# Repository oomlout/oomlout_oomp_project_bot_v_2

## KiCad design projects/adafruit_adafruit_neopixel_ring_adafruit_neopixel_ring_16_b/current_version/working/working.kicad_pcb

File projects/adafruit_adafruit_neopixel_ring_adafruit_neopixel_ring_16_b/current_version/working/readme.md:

# adafruit_neopixel_ring
 
## summary 
* id: adafruit_adafruit_neopixel_ring_adafruit_neopixel_ring_16_b
* user: adafruit
* name: adafruit_neopixel_ring
* board: adafruit_neopixel_ring_16_b
* repo: https://github.com/adafruit/Adafruit-NeoPixel-Ring

* src_file_repo_sch: 
* src_file_repo_sch_link: https://github.com/adafruit/Adafruit-NeoPixel-Ring/tree/master/
* full details link: https://github.com/oomlout/oomlout_oomp_project_bot_v_2/tree/main/projects/adafruit_adafruit_neopixel_ring_adafruit_neopixel_ring_16_b/current_version/working  

## schematic  
  
[schematic (pdf)](working_schematic.pdf) 

## pcb  

[board (pdf)](working.pdf)  

## working_bom
| Id | Designator | Footprint | Quantity | Designation | Supplier and ref |  | None | 
| --- | --- | --- | --- | --- | --- | --- | --- | 
| 1 | C6,C10,C12,C8,C9,C2,C3,C4 | C0603 | 8 |  |  |  | [''] | 
| 2 | LED11,LED2,LED9,LED4,LED6,LED1,LED10,LED12,LED7,LED3,LED5,LED8 | WS28115050 | 12 | WS28115050 |  |  | [''] | 
| 3 | JP1,JP2,JP3,JP4 | 1X01-CLEANBIG | 4 |  |  |  | [''] | 
| 4 | U$1,U$2 | GUIDE-STAR-12 | 2 |  |  |  | [''] | 
| 5 | U$3 | ADAFRUIT_5MM | 1 |  |  |  | [''] | 

## bom_schematic
| Ref | Qnty | Value | Cmp name | Footprint | Description | Vendor | DNP | 
| --- | --- | --- | --- | --- | --- | --- | --- | 
| C2, C3, C4, C6, C8, C9, C10, C12 | 8 | C-EUC0603 | C-EUC0603 | working:C0603 |  |  |  | 
| JP1, JP2, JP3, JP4 | 4 | PINHD-1X1CB | PINHD-1X1CB | working:1X01-CLEANBIG |  |  |  | 
| LED1, LED2, LED3, LED4, LED5, LED6, LED7, LED8, LED9, LED10, LED11, LED12 | 12 | WS28115050 | WS28115050 | working:WS28115050 |  |  |  |

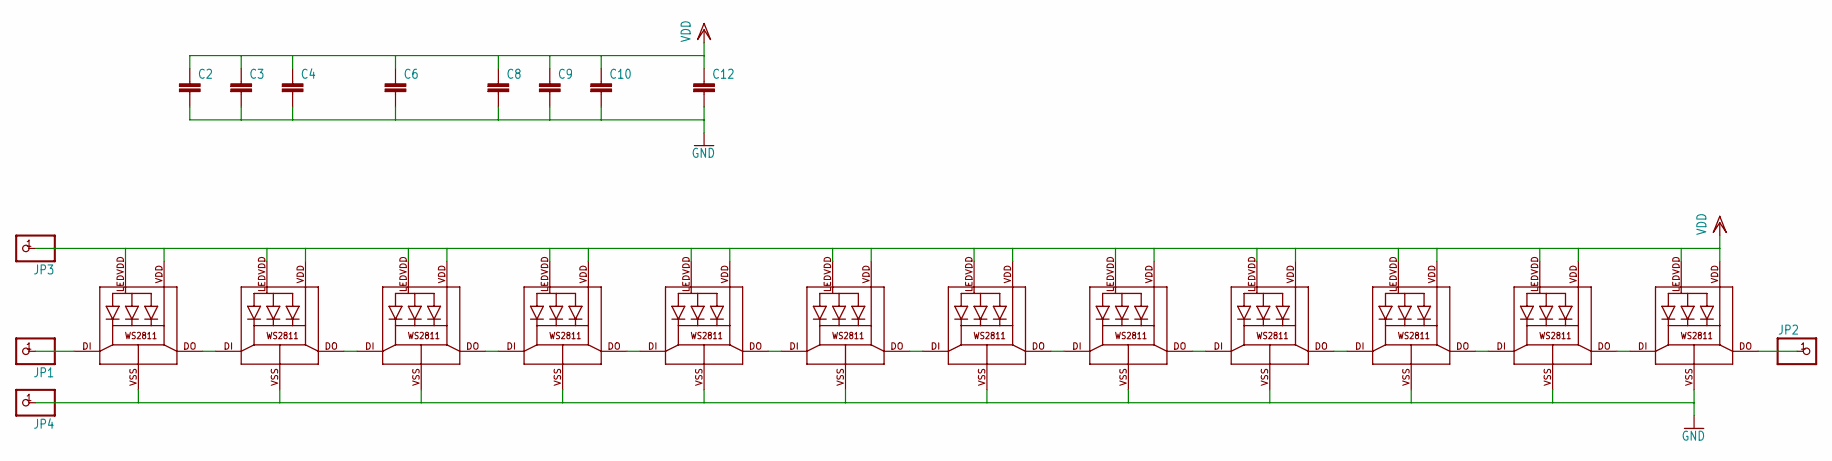
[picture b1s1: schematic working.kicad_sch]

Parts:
C2, C3, C4, C6, C8, C9, C10, C12: C-EUC0603; C0603
JP1, JP2, JP3, JP4: PINHD-1X1CB; 1X01-CLEANBIG
LED1, LED2, LED3, LED4, LED5, LED6, LED7, LED8, LED9, LED10, LED11, LED12: WS28115050

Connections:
GND: C2.2, C3.2, C4.2, C6.2, C8.2, C9.2, C10.2, C12.2, JP4.1, LED1.VSS (GND), LED2.VSS (GND), LED3.VSS (GND), LED4.VSS (GND), LED5.VSS (GND), LED6.VSS (GND), LED7.VSS (GND), LED8.VSS (GND), LED9.VSS (GND), LED10.VSS (GND), LED11.VSS (GND), LED12.VSS (GND)
unnamed: LED1.DO, LED2.DI
unnamed: LED2.DO, LED3.DI
unnamed: LED3.DO, LED4.DI
unnamed: LED4.DO, LED5.DI
unnamed: LED5.DO, LED6.DI
unnamed: LED6.DO, LED7.DI
unnamed: LED7.DO, LED8.DI
unnamed: LED8.DO, LED9.DI
unnamed: LED9.DO, LED10.DI
unnamed: LED10.DO, LED11.DI
unnamed: LED11.DO, LED12.DI
unnamed: JP1.1, LED1.DI
unnamed: JP2.1, LED12.DO
VDD: C2.1, C3.1, C4.1, C6.1, C8.1, C9.1, C10.1, C12.1, JP3.1, LED1.LEDVDD, LED1.VDD, LED2.LEDVDD, LED2.VDD, LED3.LEDVDD, LED3.VDD, LED4.LEDVDD, LED4.VDD, LED5.LEDVDD, LED5.VDD, LED6.LEDVDD, LED6.VDD, LED7.LEDVDD, LED7.VDD, LED8.LEDVDD, LED8.VDD, LED9.LEDVDD, LED9.VDD, LED10.LEDVDD, LED10.VDD, LED11.LEDVDD, LED11.VDD, LED12.LEDVDD, LED12.VDD

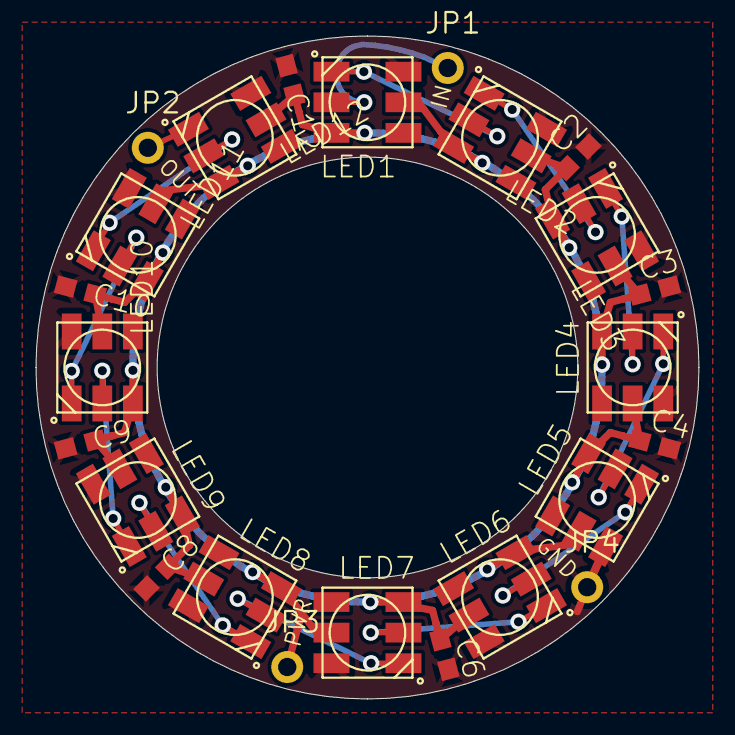
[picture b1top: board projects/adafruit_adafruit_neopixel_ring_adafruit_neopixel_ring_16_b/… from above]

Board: 2 copper layers, 36.8 x 36.8 mm, 27 parts (1 on the bottom side), 15 nets.

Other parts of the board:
U$1, U$2: GUIDE-STAR-12
U$3: ADAFRUIT_5MM

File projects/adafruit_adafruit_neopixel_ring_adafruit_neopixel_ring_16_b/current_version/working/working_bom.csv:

"Id";"Designator";"Footprint";"Quantity";"Designation";"Supplier and ref";
1;"C6,C10,C12,C8,C9,C2,C3,C4";"C0603";8;"";;;
2;"LED11,LED2,LED9,LED4,LED6,LED1,LED10,LED12,LED7,LED3,LED5,LED8";"WS28115050";12;"WS28115050";;;
3;"JP1,JP2,JP3,JP4";"1X01-CLEANBIG";4;"";;;
4;"U$1,U$2";"GUIDE-STAR-12";2;"";;;
5;"U$3";"ADAFRUIT_5MM";1;"";;;

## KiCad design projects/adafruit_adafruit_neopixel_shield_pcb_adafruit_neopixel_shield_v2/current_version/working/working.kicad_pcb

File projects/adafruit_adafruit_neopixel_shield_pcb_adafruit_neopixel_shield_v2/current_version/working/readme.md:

# adafruit_neopixel_shield_pcb
 
## summary 
* id: adafruit_adafruit_neopixel_shield_pcb_adafruit_neopixel_shield_v2
* user: adafruit
* name: adafruit_neopixel_shield_pcb
* board: adafruit_neopixel_shield_v2
* repo: https://github.com/adafruit/Adafruit-NeoPixel-Shield-PCB

* src_file_repo_sch: 
* src_file_repo_sch_link: https://github.com/adafruit/Adafruit-NeoPixel-Shield-PCB/tree/master/
* full details link: https://github.com/oomlout/oomlout_oomp_project_bot_v_2/tree/main/projects/adafruit_adafruit_neopixel_shield_pcb_adafruit_neopixel_shield_v2/current_version/working  

## schematic  
  
[schematic (pdf)](working_schematic.pdf) 

## pcb  

[board (pdf)](working.pdf)  

## working_bom
| Id | Designator | Footprint | Quantity | Designation | Supplier and ref |  | None | 
| --- | --- | --- | --- | --- | --- | --- | --- | 
| 1 | C28,C15,R1,C12,C11,C33,C17,C3,C27,C14,C20,C32,C6,C7,C26,C23,C8,C5,C24,C30,C29,C35,C18,C13,C1,C25,C2,C21,C34,C4,C22,C9,C16,C10,C19,C31 | _0805NO | 36 |  |  |  | [''] | 
| 2 | @HOLE3,@HOLE2,@HOLE0,@HOLE1 |  | 4 |  |  |  | [''] | 
| 3 | Q1 | SOT23-WIDE | 1 | IRLML6401 |  |  | [''] | 
| 4 | LED36,LED24,LED6,LED22,LED16,LED1,LED40,LED31,LED19,LED38,LED10,LED7,LED15,LED25,LED21,LED17,LED30,LED3,LED39,LED27,LED12,LED4,LED29,LED23,LED5,LED28,LED26,LED18,LED2,LED14,LED34,LED35,LED9,LED8,LED37,LED11,LED13,LED33,LED32,LED20 | WS2812B | 40 | WS2812B5050 |  |  | [''] | 
| 5 | FID2,FID1,FID3 | FIDUCIAL_1MM | 3 | FIDUCIAL" |  |  | [''] | 
| 6 | U$1 | ADAFRUIT_5MM | 1 |  |  |  | [''] | 
| 7 | SW1 | EVQ-Q2 | 1 | SPST_TACT-EVQQ2 |  |  | [''] | 
| 8 | JP1 | 1X02_ROUND | 1 |  |  |  | [''] | 
| 9 | JP2 | 1X01-CLEANBIG | 1 |  |  |  | [''] | 
| 10 | U1 | ARDUINOR3-BPLACE | 1 | ARDUINOR3-BPLACE |  |  | [''] | 
| 11 | J1 | 1X2-3.5MM | 1 | 1X2-3.5MM |  |  | [''] | 
| 12 | SJ1 | SOLDERJUMPER_CLOSEDWIRE | 1 |  |  |  | [''] | 
| 13 | U$2 | ADAFRUIT_TEXT_30MM | 1 |  |  |  | [''] | 

## bom_schematic
| Ref | Qnty | Value | Cmp name | Footprint | Description | Vendor | DNP | 
| --- | --- | --- | --- | --- | --- | --- | --- | 
| C1, C2, C3, C4, C5, C6, C7, C8, C9, C10, C11, C12, C13, C14, C15, C16, C17, C18, C19, C20, C21, C22, C23, C24, C25, C26, C27, C28, C29, C30, C31, C32, C33, C34, C35 | 35 | CAP_CERAMIC_0805NO | CAP_CERAMIC_0805NO | working:_0805NO |  |  |  | 
| FID1, FID2, FID3 | 3 | FIDUCIAL"" | FIDUCIAL{dblquote}{dblquote} | working:FIDUCIAL_1MM |  |  |  | 
| J1 | 1 | 1X2-3.5MM | 1X2-3.5MM | working:1X2-3.5MM |  |  |  | 
| JP1 | 1 | HEADER-1X2ROUND | HEADER-1X2ROUND | working:1X02_ROUND |  |  |  | 
| JP2 | 1 | PINHD-1X1CB | PINHD-1X1CB | working:1X01-CLEANBIG |  |  |  | 
| LED1, LED2, LED3, LED4, LED5, LED6, LED7, LED8, LED9, LED10, LED11, LED12, LED13, LED14, LED15, LED16, LED17, LED18, LED19, LED20, LED21, LED22, LED23, LED24, LED25, LED26, LED27, LED28, LED29, LED30, LED31, LED32, LED33, LED34, LED35, LED36, LED37, LED38, LED39, LED40 | 40 | WS2812B5050 | WS2812B5050 | working:WS2812B |  |  |  | 
| Q1 | 1 | IRLML6401 | MOSFET-PWIDE | working:SOT23-WIDE |  |  |  | 
| R1 | 1 | RESISTOR_0805NO | RESISTOR_0805NO | working:_0805NO |  |  |  | 
| SJ1 | 1 | SOLDERJUMPERCLOSED | SOLDERJUMPERCLOSED | working:SOLDERJUMPER_CLOSEDWIRE |  |  |  | 
| SW1 | 1 | SPST_TACT-EVQQ2 | SPST_TACT-EVQQ2 | working:EVQ-Q2 |  |  |  | 
| U1 | 1 | ARDUINOR3-BPLACE | ARDUINOR3-BPLACE | working:ARDUINOR3-BPLACE |  |  |  |

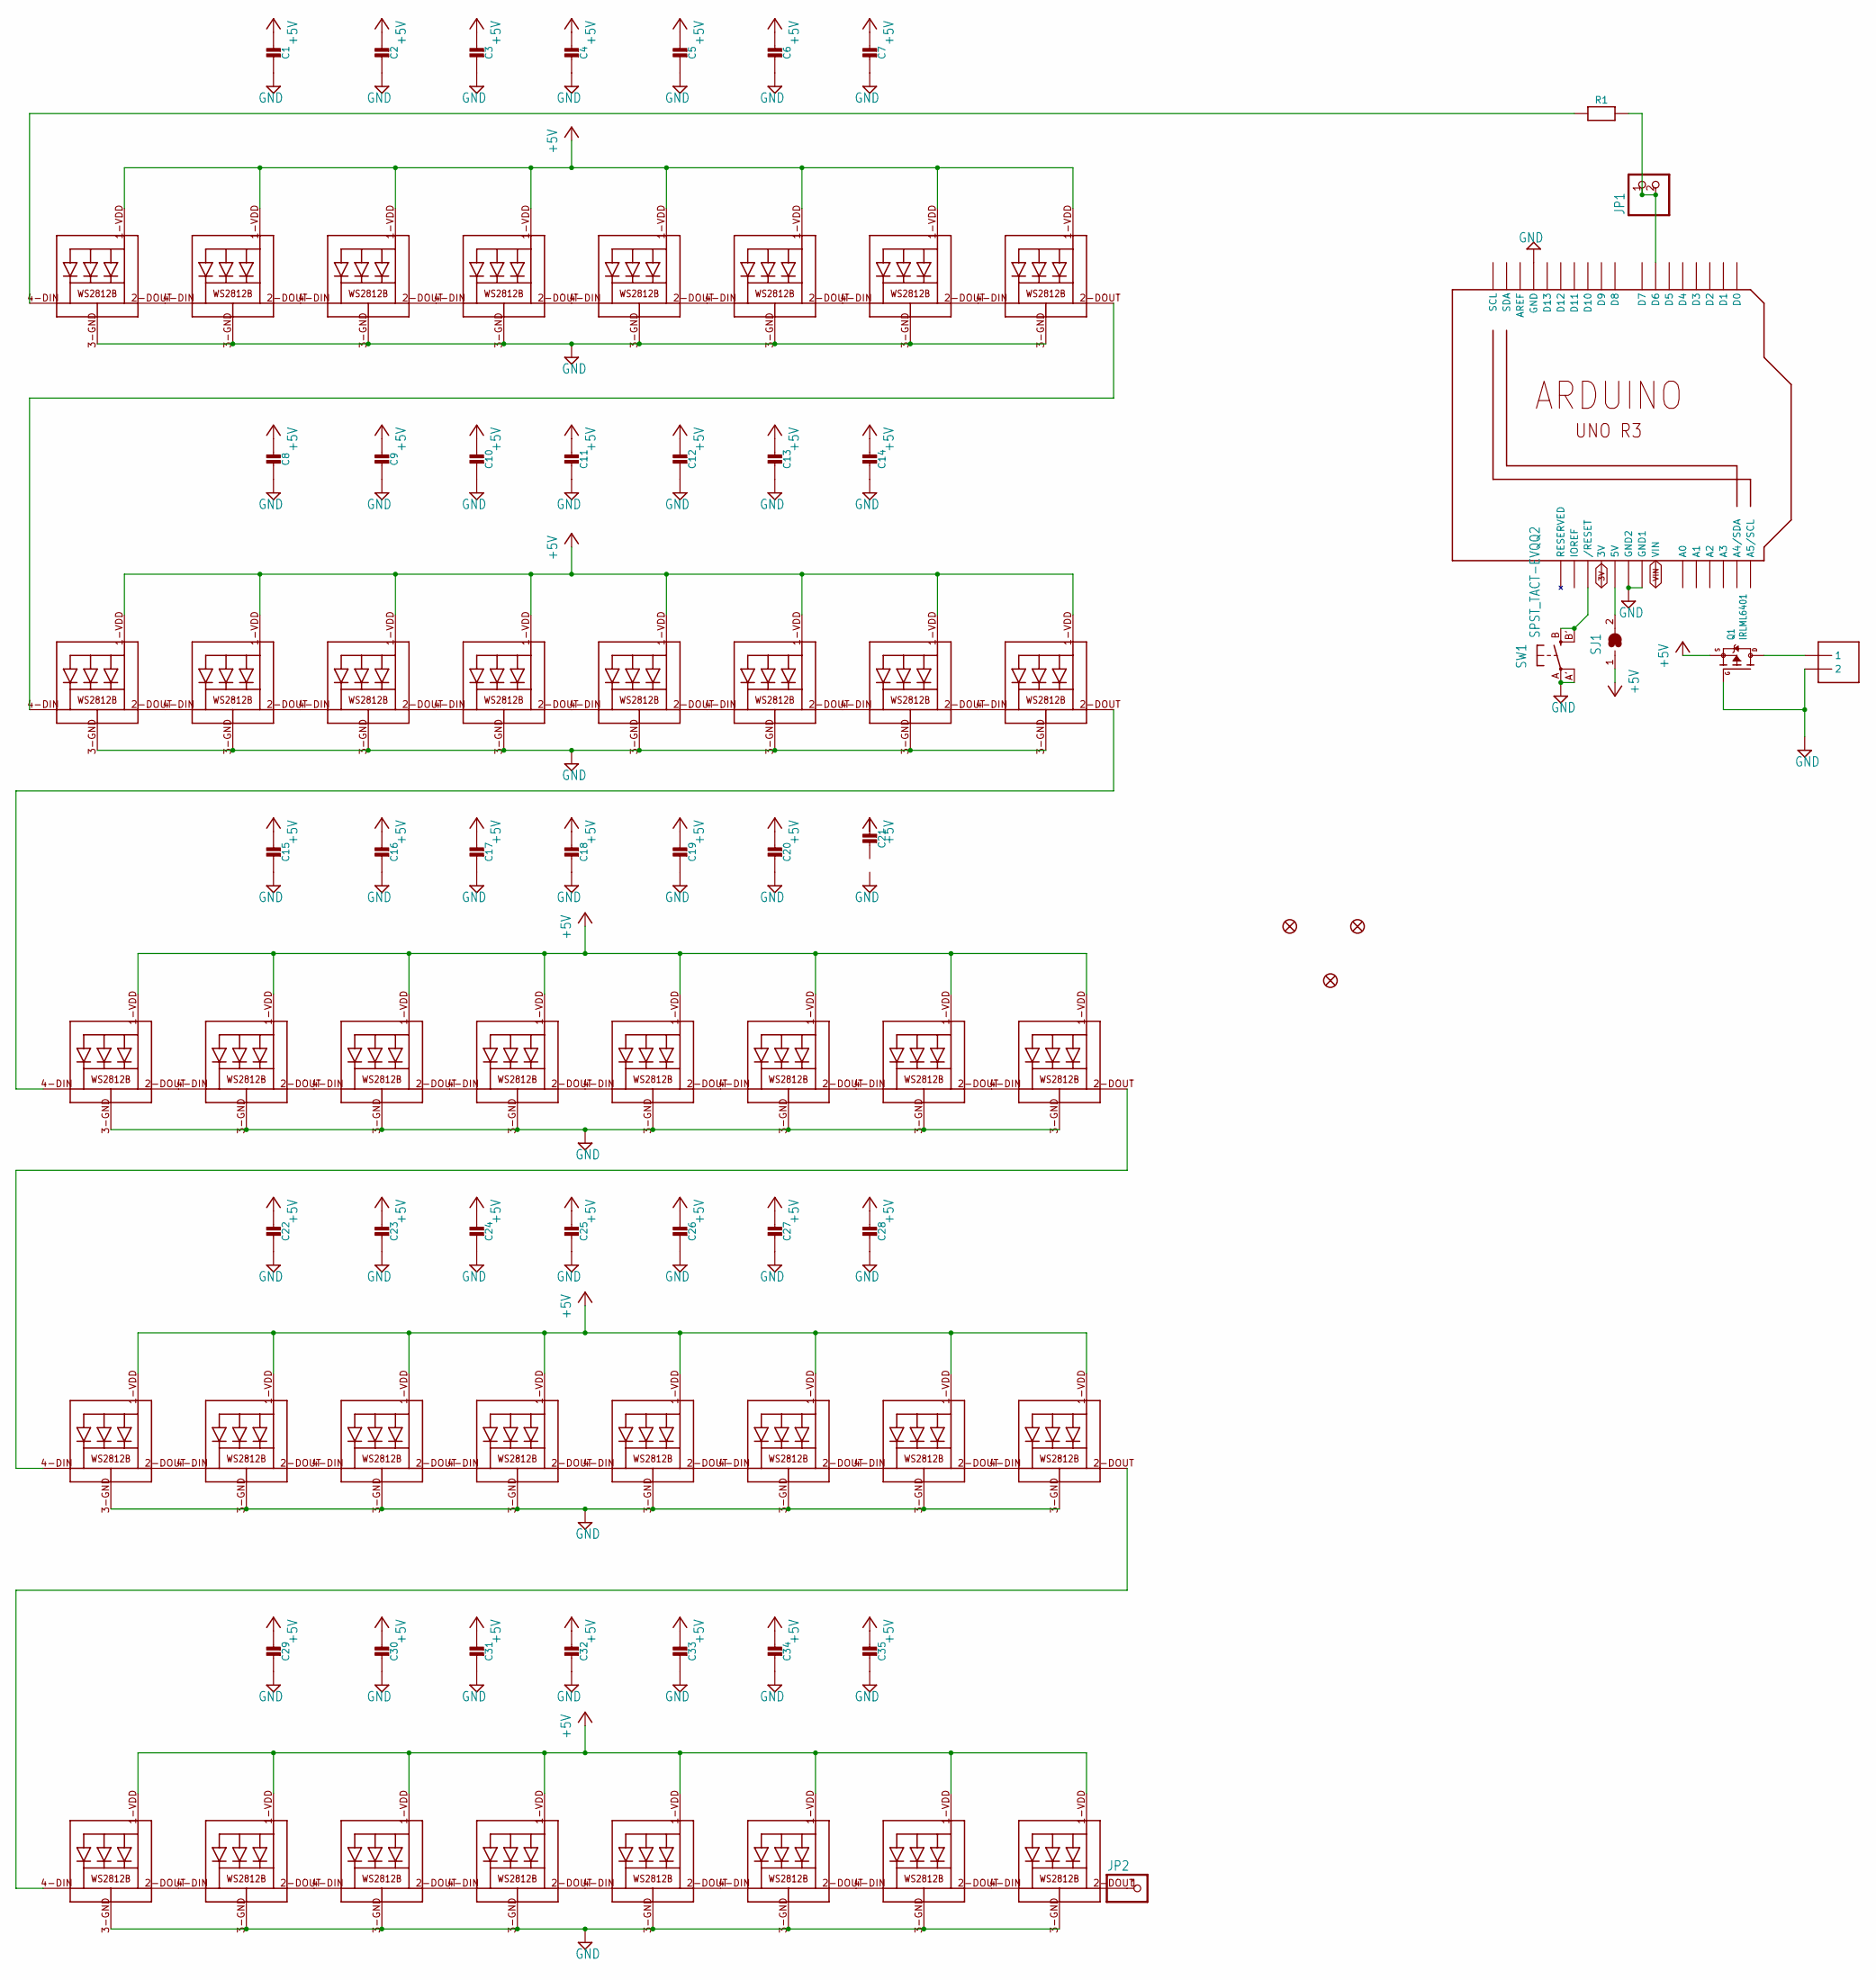
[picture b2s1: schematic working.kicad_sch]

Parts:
C1, C2, C3, C4, C5, C6, C7, C8, C9, C10, C11, C12, C13, C14, C15, C16, C17, C18, C19, C20, C21, C22, C23, C24, C25, C26, C27, C28, C29, C30, C31, C32, C33, C34, C35: CAP_CERAMIC_0805NO; _0805NO
FID1, FID2, FID3: FIDUCIAL""; FIDUCIAL_1MM
J1: 1X2-3.5MM
JP1: HEADER-1X2ROUND; 1X02_ROUND
JP2: PINHD-1X1CB; 1X01-CLEANBIG
LED1, LED2, LED3, LED4, LED5, LED6, LED7, LED8, LED9, LED10, LED11, LED12, LED13, LED14, LED15, LED16, LED17, LED18, LED19, LED20, LED21, LED22, LED23, LED24, LED25, LED26, LED27, LED28, LED29, LED30, LED31, LED32, LED33, LED34, LED35, LED36, LED37, LED38, LED39, LED40: WS2812B5050; WS2812B
Q1: IRLML6401; SOT23-WIDE
R1: RESISTOR_0805NO; _0805NO
SJ1: SOLDERJUMPERCLOSED; SOLDERJUMPER_CLOSEDWIRE
SW1: SPST_TACT-EVQQ2; EVQ-Q2
U1: ARDUINOR3-BPLACE

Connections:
3V: U1.3V
+5V: C1.1, C2.1, C3.1, C4.1, C5.1, C6.1, C7.1, C8.1, C9.1, C10.1, C11.1, C12.1, C13.1, C14.1, C15.1, C16.1, C17.1, C18.1, C19.1, C20.1, C21.1, C22.1, C23.1, C24.1, C25.1, C26.1, C27.1, C28.1, C29.1, C30.1, C31.1, C32.1, C33.1, C34.1, C35.1, LED1.1-VDD (VDD), LED2.1-VDD (VDD), LED3.1-VDD (VDD), LED4.1-VDD (VDD), LED5.1-VDD (VDD), LED6.1-VDD (VDD), LED7.1-VDD (VDD), LED8.1-VDD (VDD), LED9.1-VDD (VDD), LED10.1-VDD (VDD), LED11.1-VDD (VDD), LED12.1-VDD (VDD), LED13.1-VDD (VDD), LED14.1-VDD (VDD), LED15.1-VDD (VDD), LED16.1-VDD (VDD), LED17.1-VDD (VDD), LED18.1-VDD (VDD), LED19.1-VDD (VDD), LED20.1-VDD (VDD), LED21.1-VDD (VDD), LED22.1-VDD (VDD), LED23.1-VDD (VDD), LED24.1-VDD (VDD), LED25.1-VDD (VDD), LED26.1-VDD (VDD), LED27.1-VDD (VDD), LED28.1-VDD (VDD), LED29.1-VDD (VDD), LED30.1-VDD (VDD), LED31.1-VDD (VDD), LED32.1-VDD (VDD), LED33.1-VDD (VDD), LED34.1-VDD (VDD), LED35.1-VDD (VDD), LED36.1-VDD (VDD), LED37.1-VDD (VDD), LED38.1-VDD (VDD), LED39.1-VDD (VDD), LED40.1-VDD (VDD), Q1.2 (S), SJ1.1
GND: C1.2, C2.2, C3.2, C4.2, C5.2, C6.2, C7.2, C8.2, C9.2, C10.2, C11.2, C12.2, C13.2, C14.2, C15.2, C16.2, C17.2, C18.2, C19.2, C20.2, C21.2, C22.2, C23.2, C24.2, C25.2, C26.2, C27.2, C28.2, C29.2, C30.2, C31.2, C32.2, C33.2, C34.2, C35.2, J1.2, LED1.3-GND (GND), LED2.3-GND (GND), LED3.3-GND (GND), LED4.3-GND (GND), LED5.3-GND (GND), LED6.3-GND (GND), LED7.3-GND (GND), LED8.3-GND (GND), LED9.3-GND (GND), LED10.3-GND (GND), LED11.3-GND (GND), LED12.3-GND (GND), LED13.3-GND (GND), LED14.3-GND (GND), LED15.3-GND (GND), LED16.3-GND (GND), LED17.3-GND (GND), LED18.3-GND (GND), LED19.3-GND (GND), LED20.3-GND (GND), LED21.3-GND (GND), LED22.3-GND (GND), LED23.3-GND (GND), LED24.3-GND (GND), LED25.3-GND (GND), LED26.3-GND (GND), LED27.3-GND (GND), LED28.3-GND (GND), LED29.3-GND (GND), LED30.3-GND (GND), LED31.3-GND (GND), LED32.3-GND (GND), LED33.3-GND (GND), LED34.3-GND (GND), LED35.3-GND (GND), LED36.3-GND (GND), LED37.3-GND (GND), LED38.3-GND (GND), LED39.3-GND (GND), LED40.3-GND (GND), Q1.1 (G), SW1.A, SW1.A' (P1), U1.GND, U1.GND1, U1.GND2
unnamed: LED1.2-DOUT (DO), LED2.4-DIN (DI)
unnamed: LED2.2-DOUT (DO), LED3.4-DIN (DI)
unnamed: LED3.2-DOUT (DO), LED4.4-DIN (DI)
unnamed: LED4.2-DOUT (DO), LED5.4-DIN (DI)
unnamed: LED5.2-DOUT (DO), LED6.4-DIN (DI)
unnamed: LED6.2-DOUT (DO), LED7.4-DIN (DI)
unnamed: LED7.2-DOUT (DO), LED8.4-DIN (DI)
unnamed: LED9.2-DOUT (DO), LED10.4-DIN (DI)
unnamed: LED10.2-DOUT (DO), LED11.4-DIN (DI)
unnamed: LED11.2-DOUT (DO), LED12.4-DIN (DI)
unnamed: LED12.2-DOUT (DO), LED13.4-DIN (DI)
unnamed: LED13.2-DOUT (DO), LED14.4-DIN (DI)
unnamed: LED14.2-DOUT (DO), LED15.4-DIN (DI)
unnamed: LED15.2-DOUT (DO), LED16.4-DIN (DI)
unnamed: LED8.2-DOUT (DO), LED9.4-DIN (DI)
unnamed: LED17.2-DOUT (DO), LED18.4-DIN (DI)
unnamed: LED18.2-DOUT (DO), LED19.4-DIN (DI)
unnamed: LED19.2-DOUT (DO), LED20.4-DIN (DI)
unnamed: LED20.2-DOUT (DO), LED21.4-DIN (DI)
unnamed: LED21.2-DOUT (DO), LED22.4-DIN (DI)
unnamed: LED22.2-DOUT (DO), LED23.4-DIN (DI)
unnamed: LED23.2-DOUT (DO), LED24.4-DIN (DI)
unnamed: LED16.2-DOUT (DO), LED17.4-DIN (DI)
unnamed: LED25.2-DOUT (DO), LED26.4-DIN (DI)
unnamed: LED26.2-DOUT (DO), LED27.4-DIN (DI)
unnamed: LED27.2-DOUT (DO), LED28.4-DIN (DI)
unnamed: LED28.2-DOUT (DO), LED29.4-DIN (DI)
unnamed: LED29.2-DOUT (DO), LED30.4-DIN (DI)
unnamed: LED30.2-DOUT (DO), LED31.4-DIN (DI)
unnamed: LED31.2-DOUT (DO), LED32.4-DIN (DI)
unnamed: LED24.2-DOUT (DO), LED25.4-DIN (DI)
unnamed: LED33.2-DOUT (DO), LED34.4-DIN (DI)
unnamed: LED34.2-DOUT (DO), LED35.4-DIN (DI)
unnamed: LED35.2-DOUT (DO), LED36.4-DIN (DI)
unnamed: LED36.2-DOUT (DO), LED37.4-DIN (DI)
unnamed: LED37.2-DOUT (DO), LED38.4-DIN (DI)
unnamed: LED38.2-DOUT (DO), LED39.4-DIN (DI)
unnamed: LED39.2-DOUT (DO), LED40.4-DIN (DI)
unnamed: LED32.2-DOUT (DO), LED33.4-DIN (DI)
unnamed: SW1.B (S), SW1.B' (S1), U1.RESET (/RESET)
unnamed: SJ1.2, U1.5V
unnamed: JP2.1, LED40.2-DOUT (DO)
unnamed: LED1.4-DIN (DI), R1.1
unnamed: JP1.1, JP1.2, R1.2, U1.D6
PWRIN: J1.1, Q1.3 (D)
VIN: U1.VIN

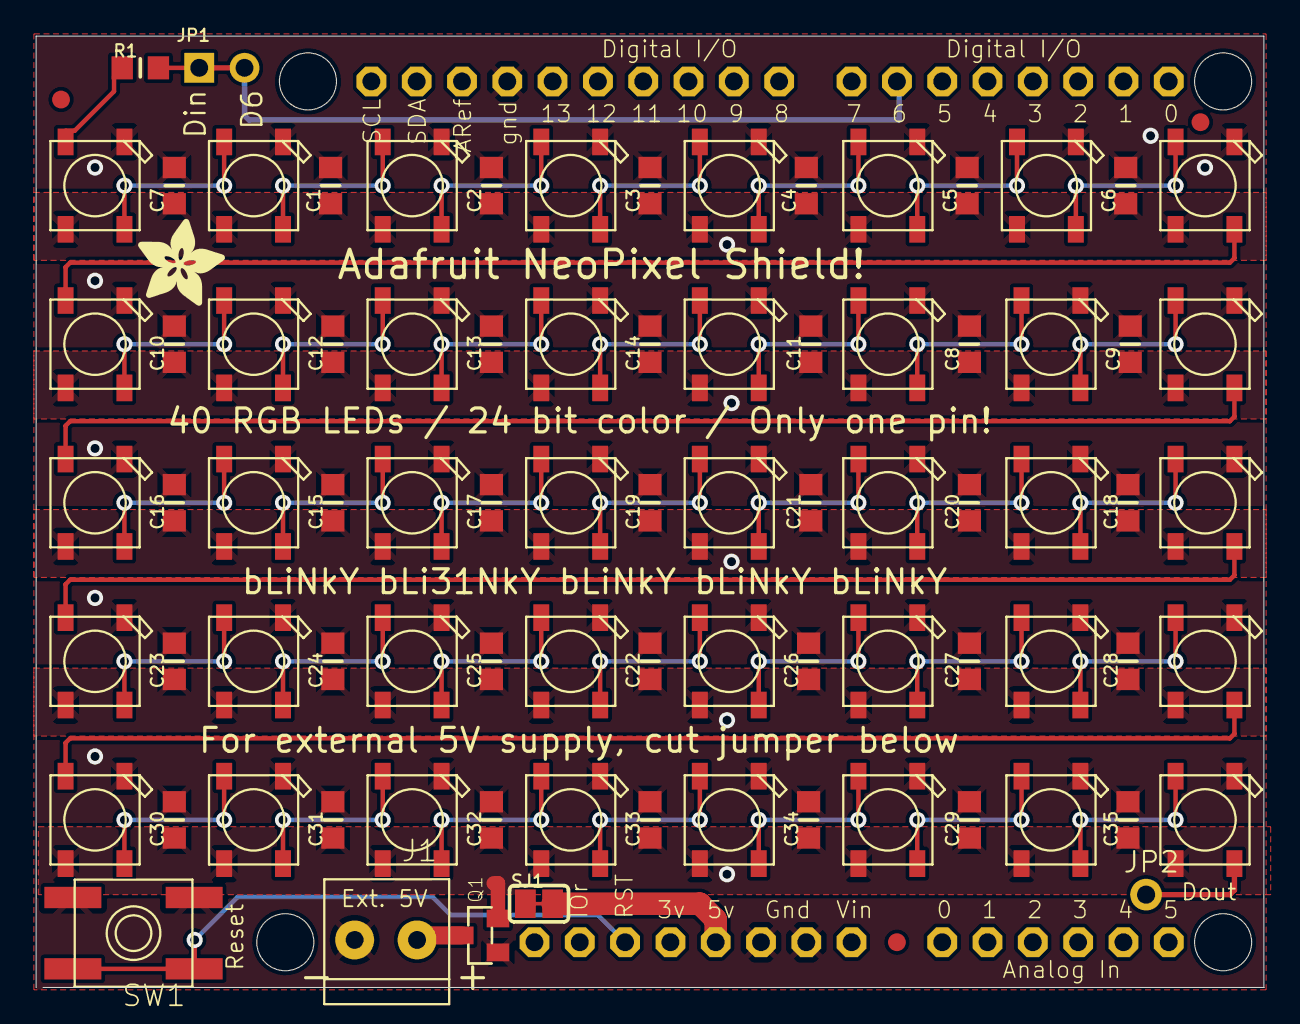
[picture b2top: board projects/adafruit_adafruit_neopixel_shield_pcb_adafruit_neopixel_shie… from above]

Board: 2 copper layers, 68.8 x 53.3 mm, 92 parts (1 on the bottom side), 47 nets.

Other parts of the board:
@HOLE0, @HOLE1, @HOLE2, @HOLE3: (no value)
U$1: ADAFRUIT_5MM
U$2: ADAFRUIT_TEXT_30MM

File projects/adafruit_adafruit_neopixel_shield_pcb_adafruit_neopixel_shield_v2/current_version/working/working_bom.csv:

"Id";"Designator";"Footprint";"Quantity";"Designation";"Supplier and ref";
1;"C28,C15,R1,C12,C11,C33,C17,C3,C27,C14,C20,C32,C6,C7,C26,C23,C8,C5,C24,C30,C29,C35,C18,C13,C1,C25,C2,C21,C34,C4,C22,C9,C16,C10,C19,C31";"_0805NO";36;"";;;
2;"@HOLE3,@HOLE2,@HOLE0,@HOLE1";"";4;"";;;
3;"Q1";"SOT23-WIDE";1;"IRLML6401";;;
4;"LED36,LED24,LED6,LED22,LED16,LED1,LED40,LED31,LED19,LED38,LED10,LED7,LED15,LED25,LED21,LED17,LED30,LED3,LED39,LED27,LED12,LED4,LED29,LED23,LED5,LED28,LED26,LED18,LED2,LED14,LED34,LED35,LED9,LED8,LED37,LED11,LED13,LED33,LED32,LED20";"WS2812B";40;"WS2812B5050";;;
5;"FID2,FID1,FID3";"FIDUCIAL_1MM";3;"FIDUCIAL""";;;
6;"U$1";"ADAFRUIT_5MM";1;"";;;
7;"SW1";"EVQ-Q2";1;"SPST_TACT-EVQQ2";;;
8;"JP1";"1X02_ROUND";1;"";;;
9;"JP2";"1X01-CLEANBIG";1;"";;;
10;"U1";"ARDUINOR3-BPLACE";1;"ARDUINOR3-BPLACE";;;
11;"J1";"1X2-3.5MM";1;"1X2-3.5MM";;;
12;"SJ1";"SOLDERJUMPER_CLOSEDWIRE";1;"";;;
13;"U$2";"ADAFRUIT_TEXT_30MM";1;"";;;

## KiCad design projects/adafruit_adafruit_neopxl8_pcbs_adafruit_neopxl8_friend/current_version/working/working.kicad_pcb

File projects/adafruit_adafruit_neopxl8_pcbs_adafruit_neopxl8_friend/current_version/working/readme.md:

# adafruit_neopxl8_pcbs
 
## summary 
* id: adafruit_adafruit_neopxl8_pcbs_adafruit_neopxl8_friend
* user: adafruit
* name: adafruit_neopxl8_pcbs
* board: adafruit_neopxl8_friend
* repo: https://github.com/adafruit/Adafruit-NeoPXL8-PCBs

* src_file_repo_sch: 
* src_file_repo_sch_link: https://github.com/adafruit/Adafruit-NeoPXL8-PCBs/tree/master/
* full details link: https://github.com/oomlout/oomlout_oomp_project_bot_v_2/tree/main/projects/adafruit_adafruit_neopxl8_pcbs_adafruit_neopxl8_friend/current_version/working  

## schematic  
  
[schematic (pdf)](working_schematic.pdf) 

## pcb  

[board (pdf)](working.pdf)  

## working_bom
| Id | Designator | Footprint | Quantity | Designation | Supplier and ref |  | None | 
| --- | --- | --- | --- | --- | --- | --- | --- | 
| 1 | C1,C2,C3 | 0603-NO | 3 | 1uF |  |  | [''] | 
| 2 | IC3 | SOT23-6 | 1 | AP3602 |  |  | [''] | 
| 3 | JP1 | 1X10_ROUND70 | 1 |  |  |  | [''] | 
| 4 | FID2,FID1 | FIDUCIAL_1MM | 2 | FIDUCIAL_1MM |  |  | [''] | 
| 5 | R1,R2 | RESPACK_4X0603 | 2 | 100 |  |  | [''] | 
| 6 | U$3,U$7 | MOUNTINGHOLE_2.5_PLATED | 2 | MOUNTINGHOLE2.5 |  |  | [''] | 
| 7 | U$11 | PCBFEAT-REV-040 | 1 |  |  |  | [''] | 
| 8 | U1 | TSSOP20 | 1 | 74HCT245 |  |  | [''] | 
| 9 | U$12 | ADAFRUIT_5MM | 1 |  |  |  | [''] | 
| 10 | CN1,CN2 | RJ45_VERTICAL_UNSHIELDED | 2 | RJ45_V_UNSH |  |  | [''] | 
| 11 | NEO_OUT2 | 2X08 | 1 |  |  |  | [''] | 

## bom_schematic
| Ref | Qnty | Value | Cmp name | Footprint | Description | Vendor | DNP | 
| --- | --- | --- | --- | --- | --- | --- | --- | 
| C1, C2, C3 | 3 | 1uF | CAP_CERAMIC0603_NO | working:0603-NO |  |  |  | 
| CN1, CN2 | 2 | RJ45_V_UNSH | RJ45_V_UNSH | working:RJ45_VERTICAL_UNSHIELDED |  |  |  | 
| FID1, FID2 | 2 | FIDUCIAL_1MM | FIDUCIAL_1MM | working:FIDUCIAL_1MM |  |  |  | 
| IC3 | 1 | AP3602 | AP3602 | working:SOT23-6 |  |  |  | 
| JP1 | 1 | HEADER-1X1070MIL | HEADER-1X1070MIL | working:1X10_ROUND70 |  |  |  | 
| NEO_OUT2 | 1 | HEADER-2X8 | HEADER-2X8 | working:2X08 |  |  |  | 
| R1, R2 | 2 | 100 | RESISTOR_4PACK | working:RESPACK_4X0603 |  |  |  | 
| U1 | 1 | 74HCT245 | 74LCX245 | working:TSSOP20 |  |  |  | 
| U$3, U$7 | 2 | MOUNTINGHOLE2.5 | MOUNTINGHOLE2.5 | working:MOUNTINGHOLE_2.5_PLATED |  |  |  | 

## mounting_holes
| x | y | package | value | ref | size | 
| --- | --- | --- | --- | --- | --- | 
| 0.0 | 26.67 | MOUNTINGHOLE_2.5_PLATED | MOUNTINGHOLE2.5 | U$3 | m3 | 
| 0.0 | 0.0 | MOUNTINGHOLE_2.5_PLATED | MOUNTINGHOLE2.5 | U$7 | m3 |

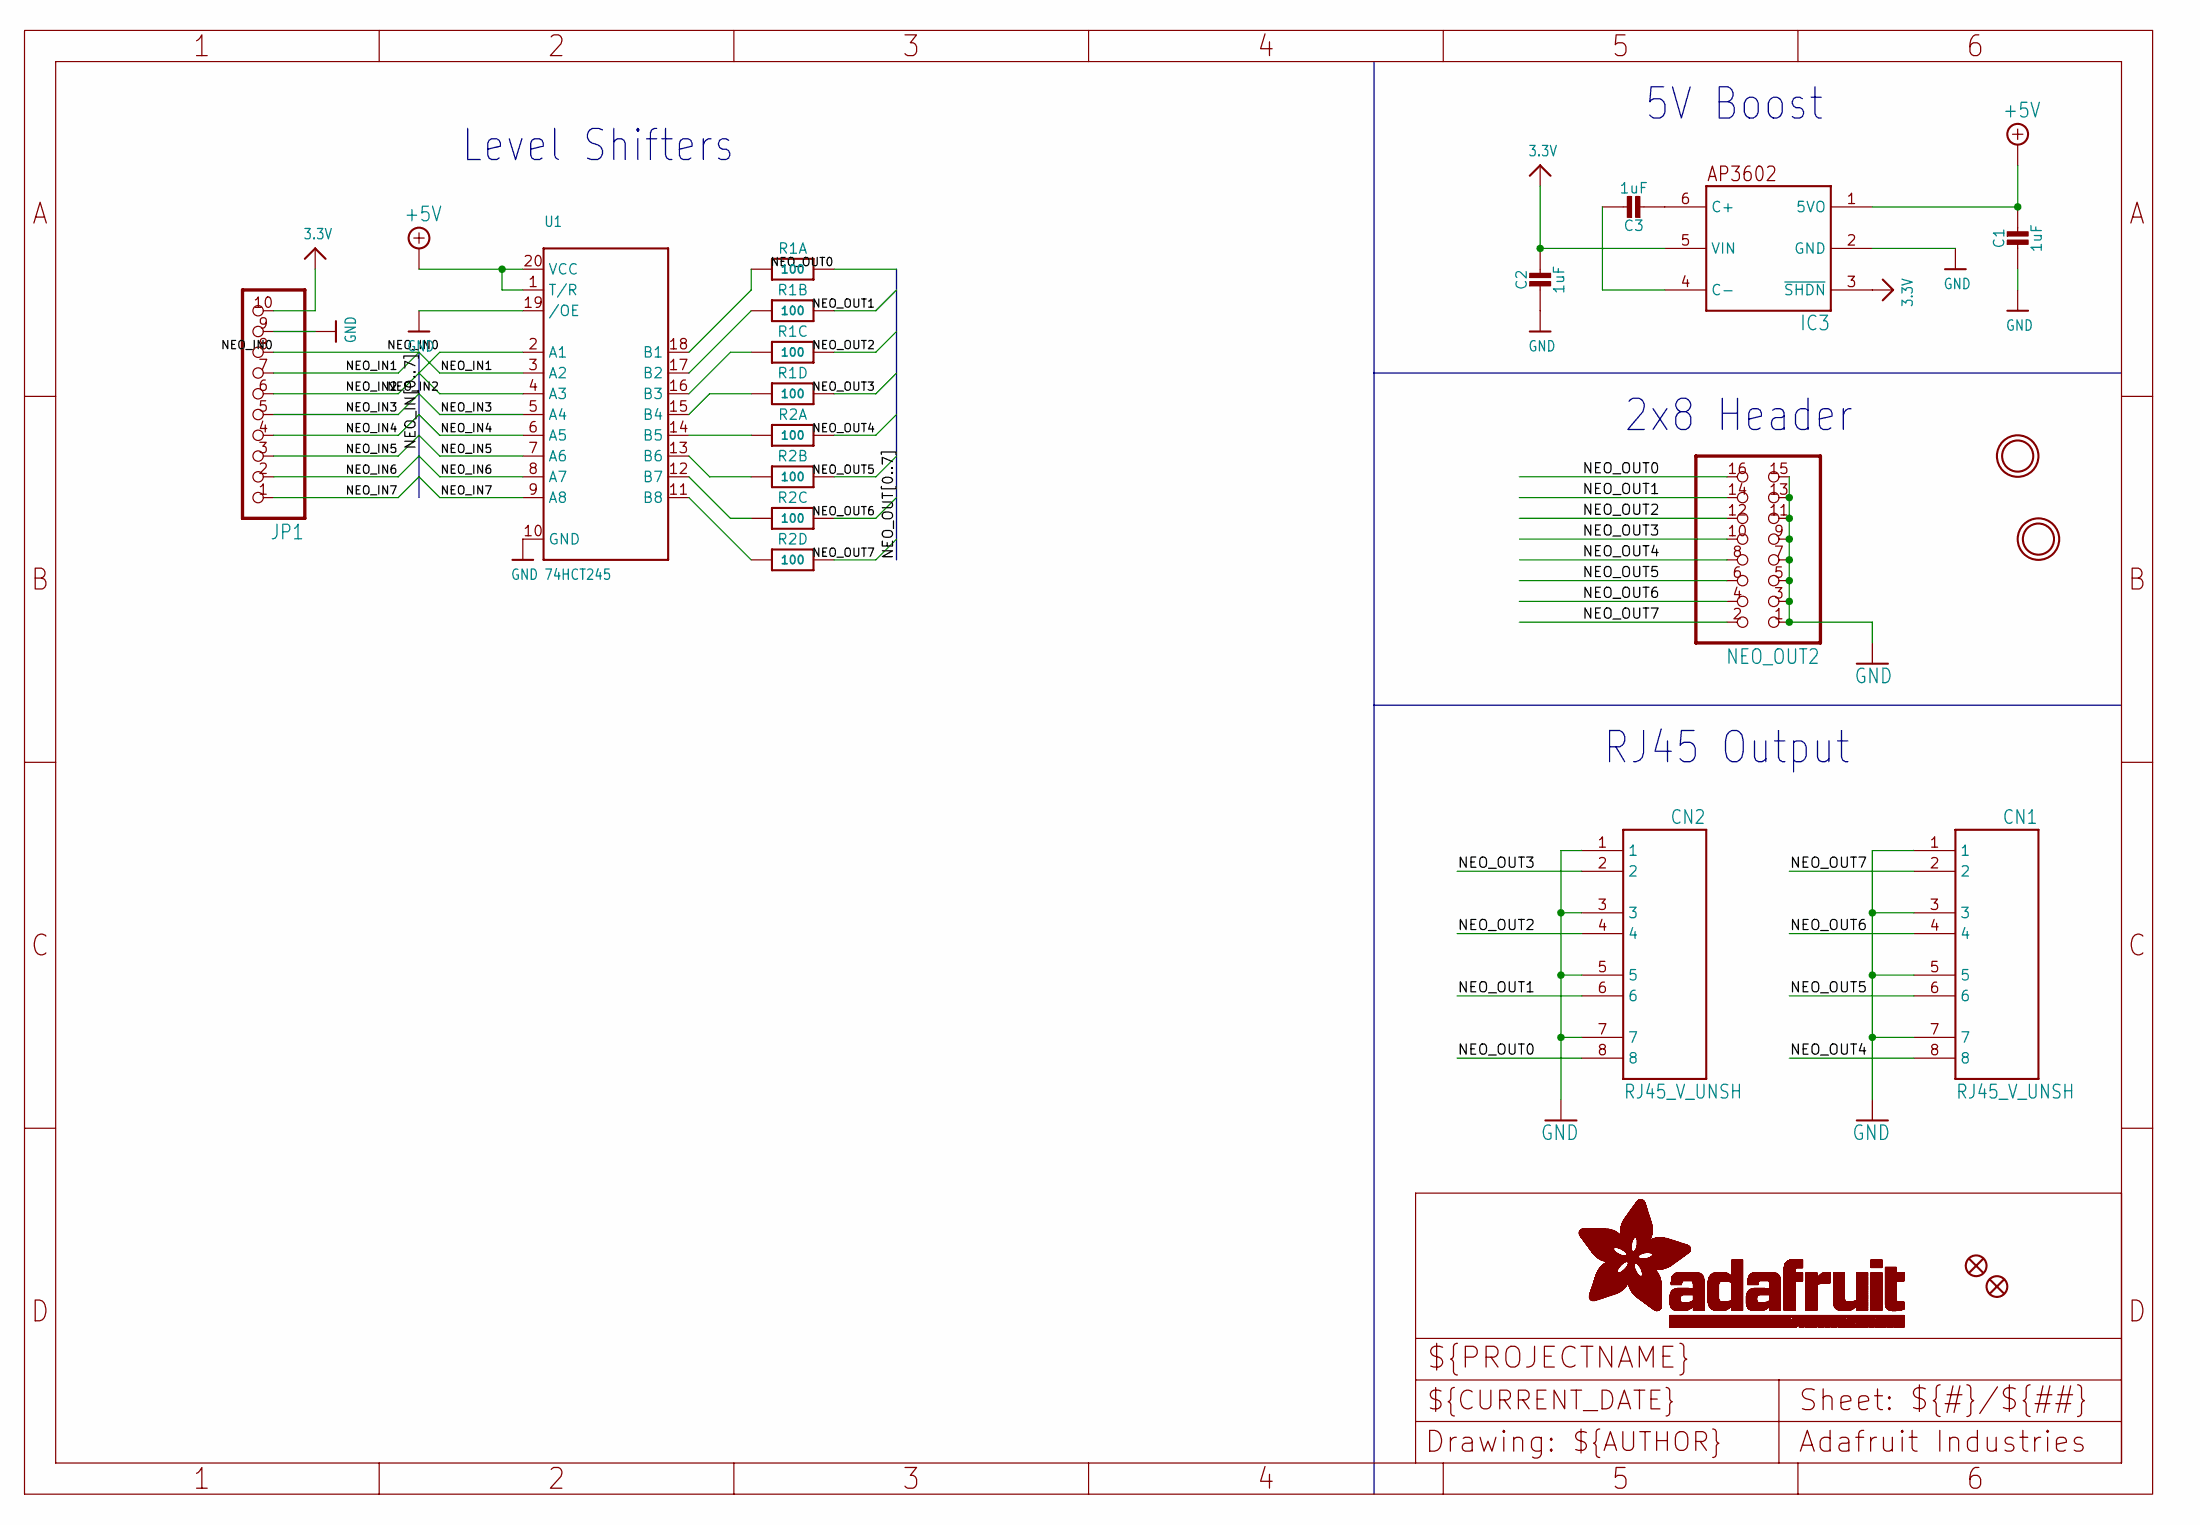
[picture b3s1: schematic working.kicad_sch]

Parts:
C1, C2, C3: 1uF; 0603-NO
CN1, CN2: RJ45_V_UNSH; RJ45_VERTICAL_UNSHIELDED
FID1, FID2: FIDUCIAL_1MM
IC3: AP3602; SOT23-6
JP1: HEADER-1X1070MIL; 1X10_ROUND70
NEO_OUT2: HEADER-2X8; 2X08
R1, R2: 100; RESPACK_4X0603
U1: 74HCT245; TSSOP20
U$3, U$7: MOUNTINGHOLE2.5; MOUNTINGHOLE_2.5_PLATED

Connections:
3.3V: C2.1, IC3.3 (~SHDN), IC3.5 (VIN), JP1.10
+5V: C1.1, IC3.1 (5VO), U1.1 (T/R), U1.20 (VCC)
GND: C1.2, C2.2, CN1.1, CN1.3, CN1.5, CN1.7, CN2.1, CN2.3, CN2.5, CN2.7, IC3.2 (GND), JP1.9, NEO_OUT2.1, NEO_OUT2.3, NEO_OUT2.5, NEO_OUT2.7, NEO_OUT2.9, NEO_OUT2.11, NEO_OUT2.13, NEO_OUT2.15, U1.10 (GND), U1.19 (/OE)
unnamed: R2.4 (1), U1.11 (B8)
unnamed: R2.3 (1), U1.12 (B7)
unnamed: R2.2 (1), U1.13 (B6)
unnamed: R2.1, U1.14 (B5)
unnamed: R1.4 (1), U1.15 (B4)
unnamed: R1.3 (1), U1.16 (B3)
unnamed: R1.2 (1), U1.17 (B2)
unnamed: R1.1, U1.18 (B1)
unnamed: C3.2, IC3.6 (C+)
unnamed: C3.1, IC3.4 (C-)
NEO_IN0: JP1.8, U1.2 (A1)
NEO_IN1: JP1.7, U1.3 (A2)
NEO_IN2: JP1.6, U1.4 (A3)
NEO_IN3: JP1.5, U1.5 (A4)
NEO_IN4: JP1.4, U1.6 (A5)
NEO_IN5: JP1.3, U1.7 (A6)
NEO_IN6: JP1.2, U1.8 (A7)
NEO_IN7: JP1.1, U1.9 (A8)
NEO_OUT0: CN2.8, NEO_OUT2.16, R1.8 (2)
NEO_OUT1: CN2.6, NEO_OUT2.14, R1.7 (2)
NEO_OUT2: CN2.4, NEO_OUT2.12, R1.6 (2)
NEO_OUT3: CN2.2, NEO_OUT2.10, R1.5 (2)
NEO_OUT4: CN1.8, NEO_OUT2.8, R2.8 (2)
NEO_OUT5: CN1.6, NEO_OUT2.6, R2.7 (2)
NEO_OUT6: CN1.4, NEO_OUT2.4, R2.6 (2)
NEO_OUT7: CN1.2, NEO_OUT2.2, R2.5 (2)

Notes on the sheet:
Level Shifters
2x8 Header
RJ45 Output
5V Boost

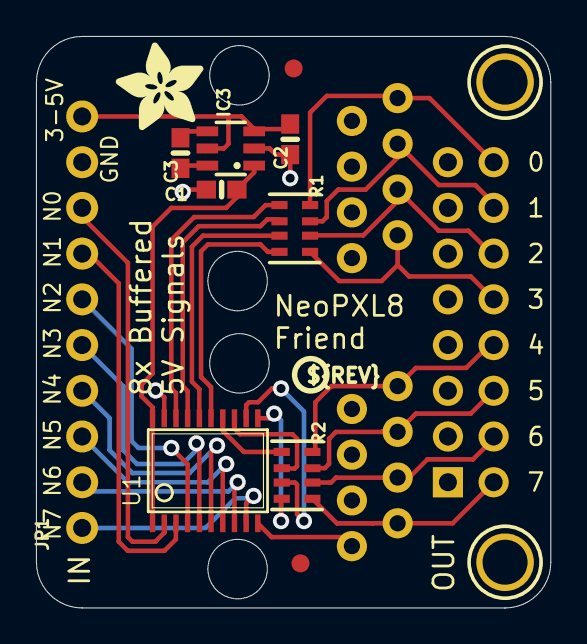
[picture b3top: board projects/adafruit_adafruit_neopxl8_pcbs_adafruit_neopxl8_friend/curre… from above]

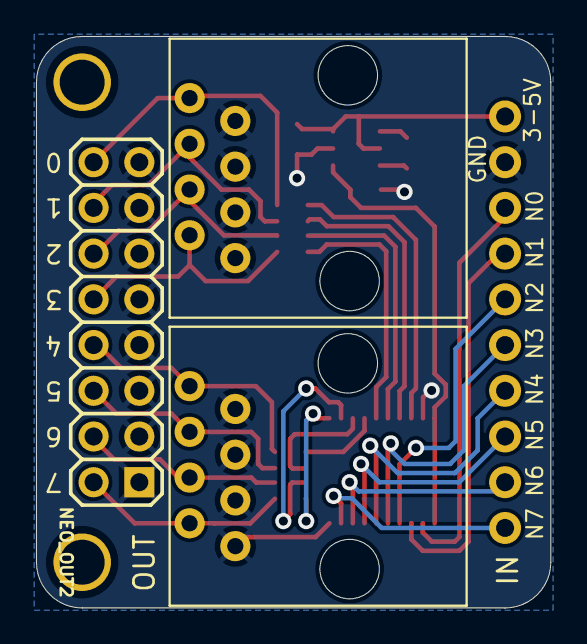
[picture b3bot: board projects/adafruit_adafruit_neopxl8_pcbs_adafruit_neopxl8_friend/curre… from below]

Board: 2 copper layers, 28.6 x 31.8 mm, 17 parts (3 on the bottom side), 29 nets.

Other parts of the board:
U$11: PCBFEAT-REV-040
U$12: ADAFRUIT_5MM
